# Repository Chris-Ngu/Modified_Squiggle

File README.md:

# Codename: Leftovers

* This is a modified Squiggle (mainly standard Squiggle) to adjust the thumb clusters and add a rotary encoder

## Changes from standard Squiggle
* Changed footprint to reversible 1u MX
* Moved thumb clusters closer (Similar to Sweep)
* Added rotary encoder
* General aesthetic changes (shape, silkscreen)

## Left off
* Working on adding encoder onto schematics and wiring onto pro micro

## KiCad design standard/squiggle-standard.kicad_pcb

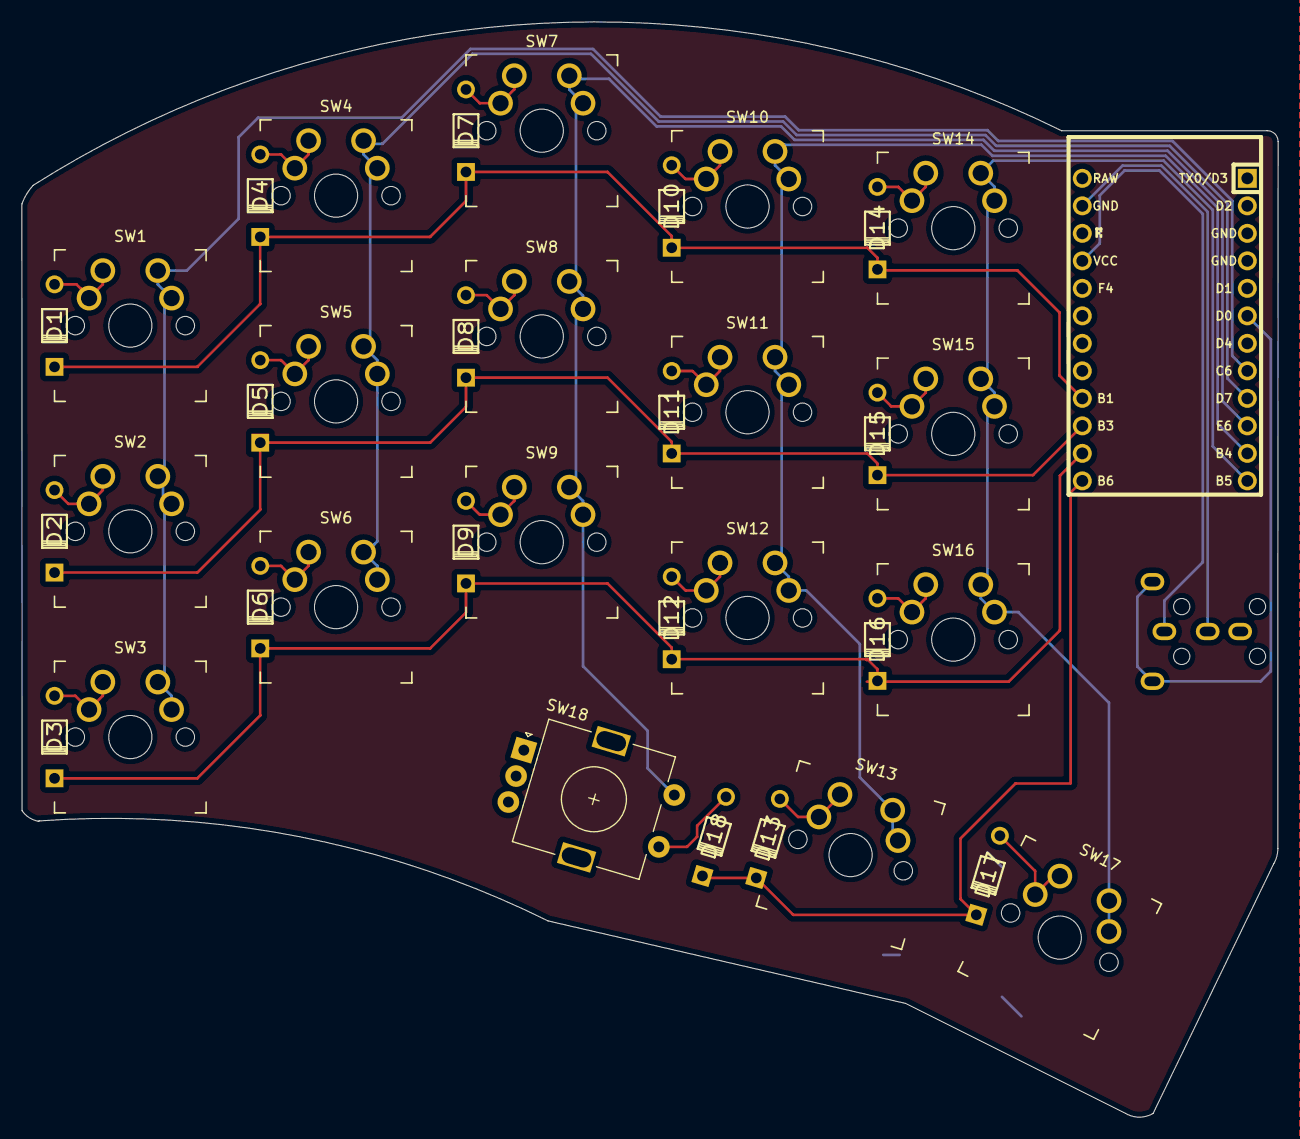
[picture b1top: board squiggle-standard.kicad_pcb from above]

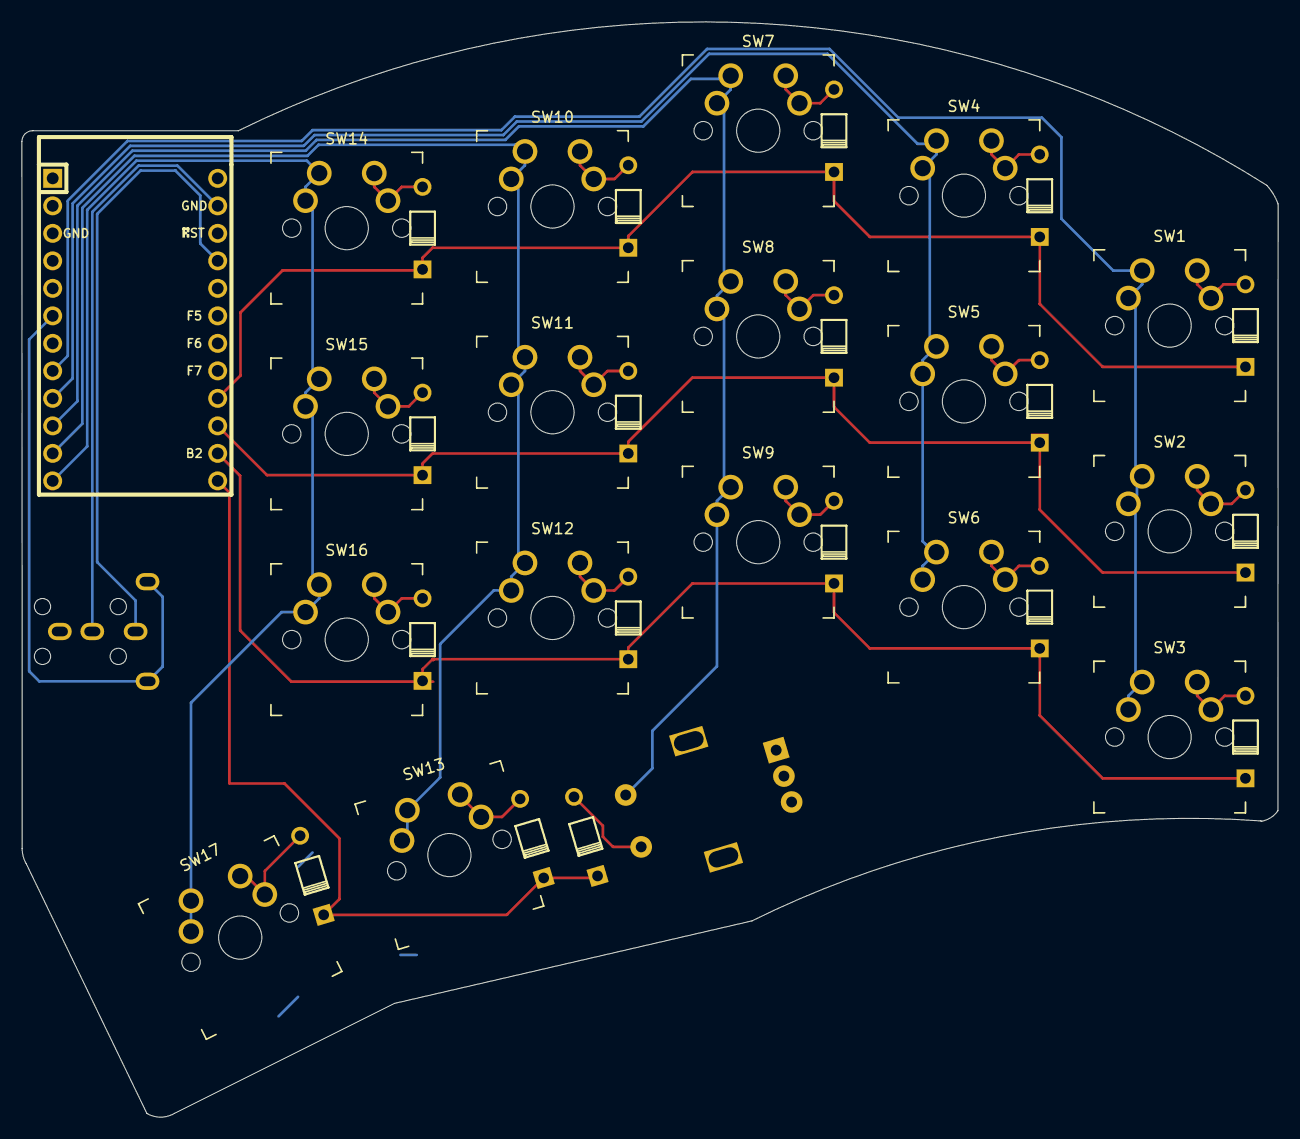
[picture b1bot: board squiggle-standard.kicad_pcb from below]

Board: 2 copper layers, 116.0 x 101.2 mm, 38 parts (2 on the bottom side), 29 nets.

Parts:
D1, D2, D3, D4, D5, D6, D7, D8, D9, D10, D11, D12, D13, D14, D15, D16, D17, D18: D; diode
SW1, SW2, SW3, SW4, SW5, SW6, SW7, SW8, SW9, SW10, SW11, SW12, SW13, SW14, SW15, SW16, SW17: switch; SW_MX_reversible
SW18: switch; RotaryEncoder_Alps_EC11E-Switch_Vertical_H20mm
U1: TRRS; trrs
U2: ProMicro; promicro

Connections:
COL0: SW1.2, SW2.2, SW3.2, U2.8
COL1: SW4.2, SW5.2, SW6.2, U2.9
COL2: SW7.2, SW8.2, SW9.2, SW18.S2, U2.10
COL3: SW10.2, SW11.2, SW12.2, SW13.2, U2.11
COL4: SW14.2, SW15.2, SW16.2, SW17.2, U2.12
unnamed: D1.2, SW1.1
unnamed: D2.2, SW2.1
unnamed: D3.2, SW3.1
unnamed: D4.2, SW4.1
unnamed: D5.2, SW5.1
unnamed: D6.2, SW6.1
unnamed: D7.2, SW7.1
unnamed: D8.2, SW8.1
unnamed: D9.2, SW9.1
unnamed: D10.2, SW10.1
unnamed: D11.2, SW11.1
unnamed: D12.2, SW12.1
unnamed: D13.2, SW13.1
unnamed: D14.2, SW14.1
unnamed: D15.2, SW15.1
unnamed: D16.2, SW16.1
unnamed: D17.2, SW17.1
unnamed: U1.2, U2.21
unnamed: U1.3, U2.23
ROW0: D1.1, D4.1, D7.1, D10.1, D14.1, U2.16
ROW1: D2.1, D5.1, D8.1, D11.1, D15.1, U2.15
ROW2: D3.1, D6.1, D9.1, D12.1, D16.1, U2.14
ROW3: D13.1, D17.1, D18.1, U2.13
SDA: U1.1, U2.6

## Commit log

2022-09-24 adding standard squiggle files
2022-09-25 adding files
2022-09-25 modifying standard design
2022-09-25 minor thumb adjustments
2022-09-25 added placeholder for rotary encoder, swapped diodes orientations
2022-09-25 adjust readme
2022-09-25 adding universal mx footprint, fixed column and row wiring, adjusted bottom left cut shape
2022-09-29 replaced switch with encoder
2022-10-02 added encoder to schematic and wired switch pinouts
